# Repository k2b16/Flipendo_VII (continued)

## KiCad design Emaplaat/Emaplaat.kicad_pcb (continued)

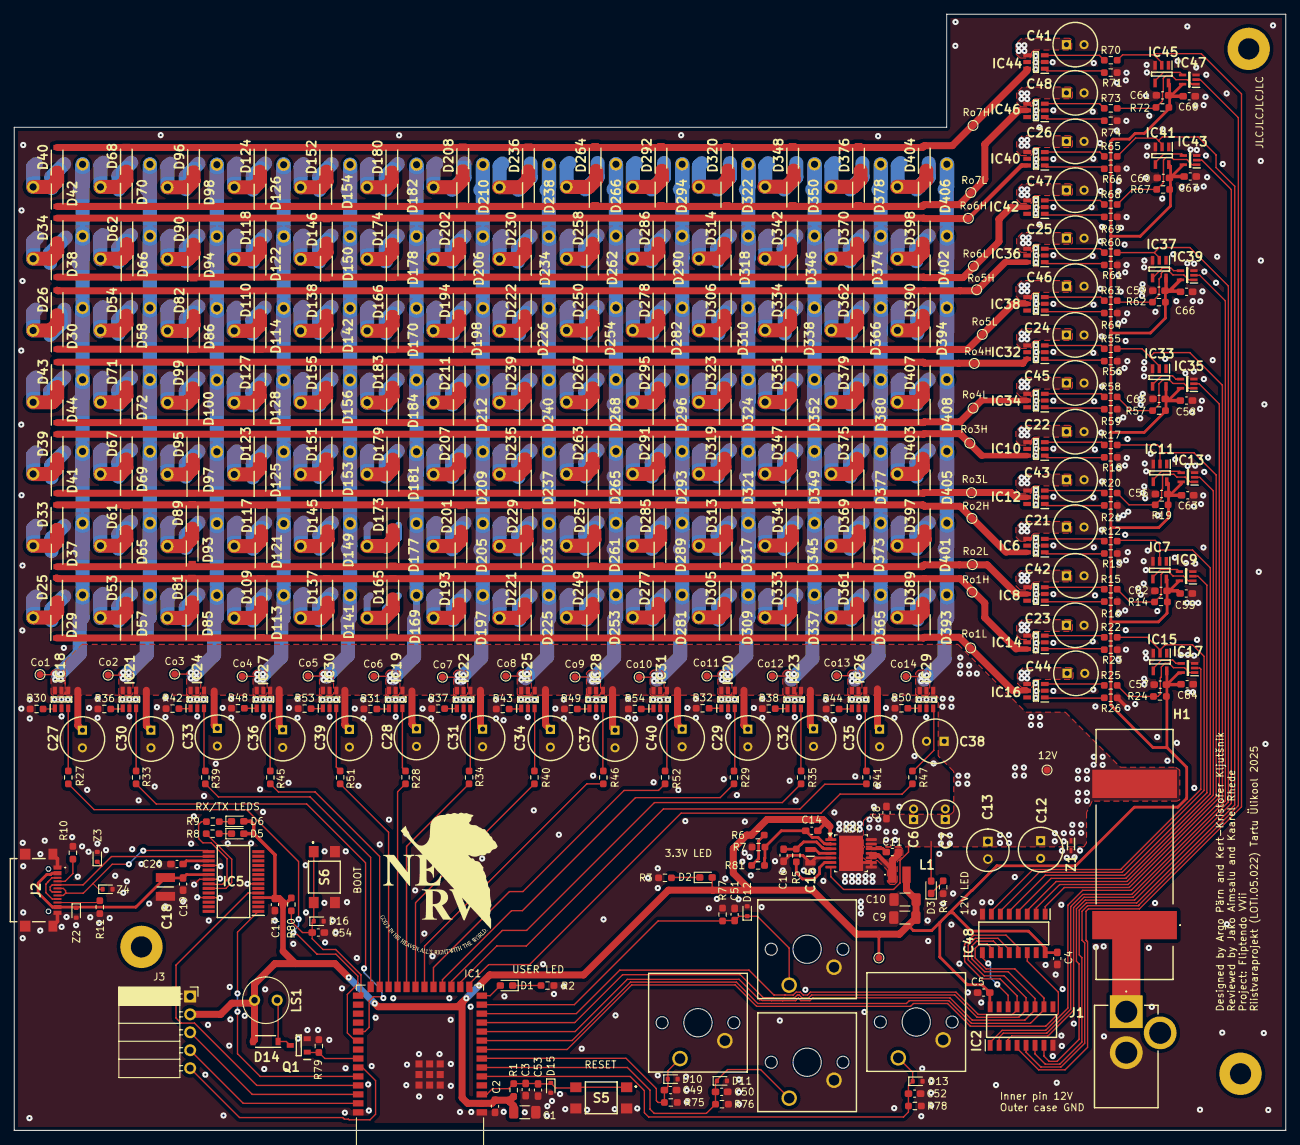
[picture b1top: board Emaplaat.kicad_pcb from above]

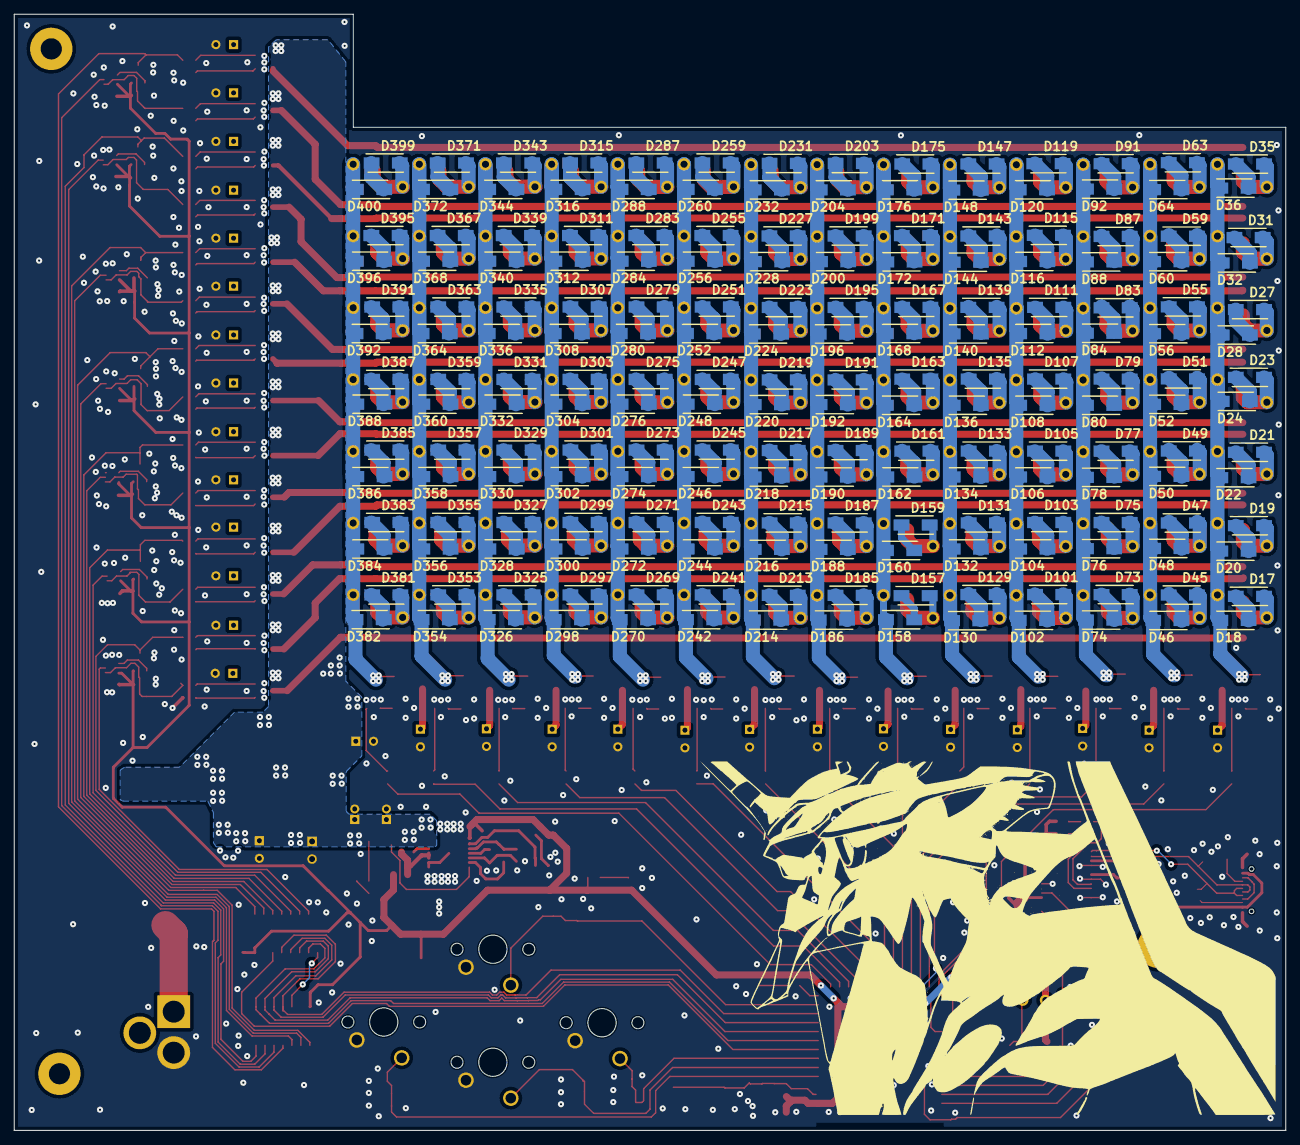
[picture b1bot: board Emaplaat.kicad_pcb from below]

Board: 2 copper layers, 180.0 x 158.0 mm, 664 parts (196 on the bottom side), 367 nets.

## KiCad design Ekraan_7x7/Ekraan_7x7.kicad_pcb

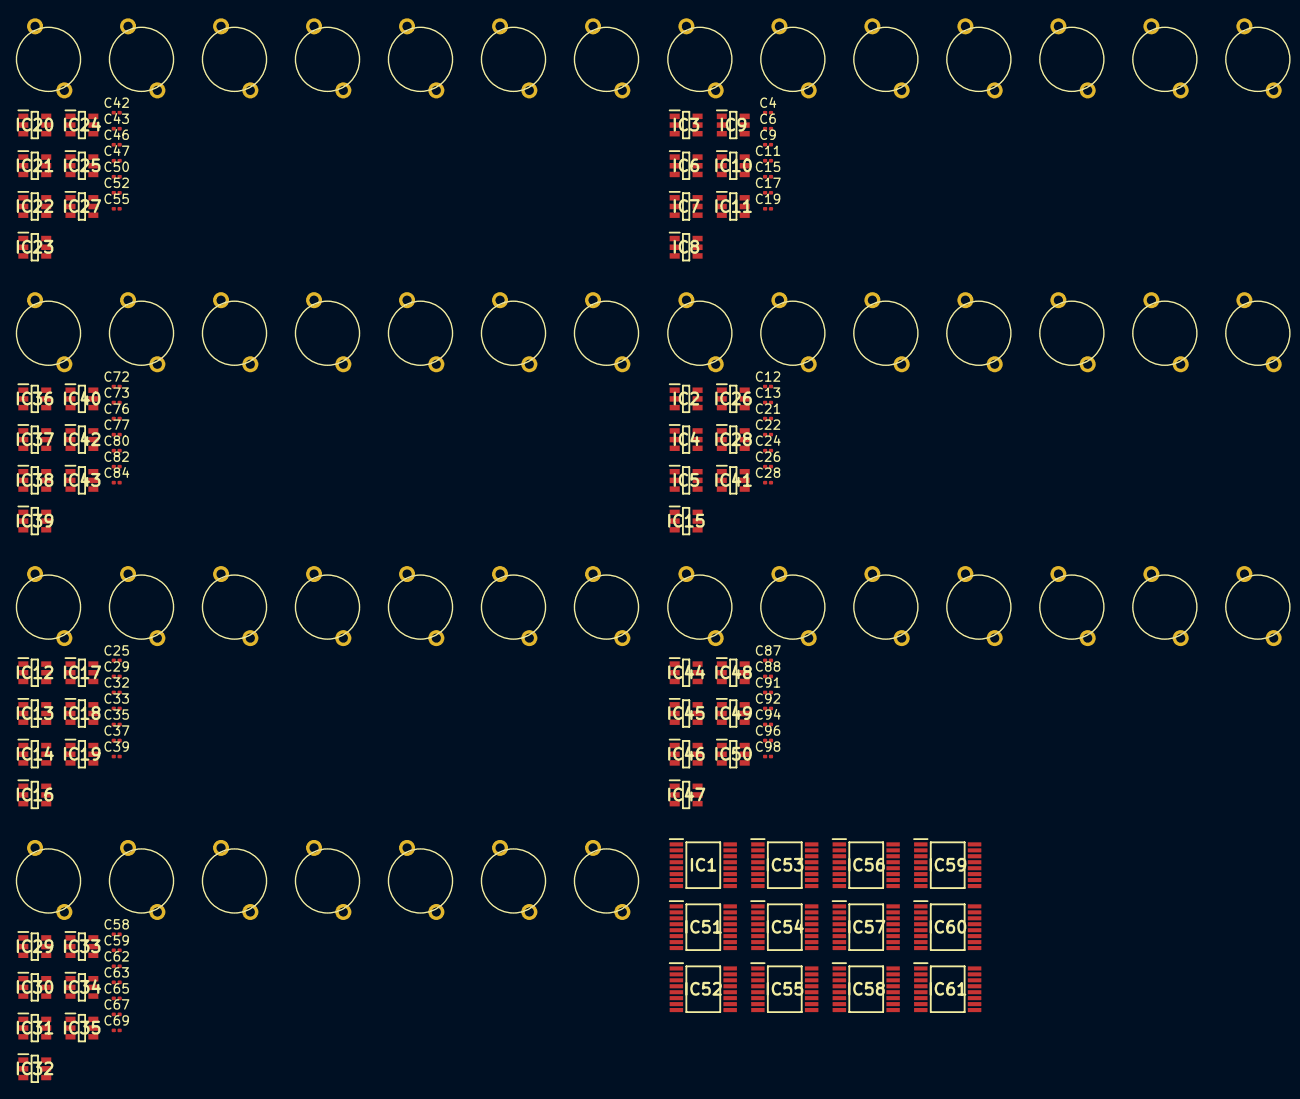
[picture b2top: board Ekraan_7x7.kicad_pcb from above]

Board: 2 copper layers, 117 parts (0 on the bottom side), 117 nets, no tracks yet.

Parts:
C4, C6, C9, C11, C12, C13, C15, C17, C19, C21, C22, C24, C25, C26, C28, C29, C32, C33, C35, C37, C39, C42, C43, C46, C47, C50, C52, C55, C58, C59, C62, C63, C65, C67, C69, C72, C73, C76, C77, C80, C82, C84, C87, C88, C91, C92, C94, C96, C98: 20u; C_0201_0603Metric
IC1, IC51, IC52, IC53, IC54, IC55, IC56, IC57, IC58, IC59, IC60, IC61: 74HC595PW-Q100,118; SOP65P640X110-16N
IC2, IC3, IC4, IC5, IC6, IC7, IC8, IC9, IC10, IC11, IC12, IC13, IC14, IC15, IC16, IC17, IC18, IC19, IC20, IC21, IC22, IC23, IC24, IC25, IC26, IC27, IC28, IC29, IC30, IC31, IC32, IC33, IC34, IC35, IC36, IC37, IC38, IC39, IC40, IC41, IC42, IC43, IC44, IC45, IC46, IC47, IC48, IC49, IC50: 1EDN7550BXTSA1; SOT95P280X145-6N
U1, U2, U3, U4, U5, U6, U7: 1EDN7550BXTSA1; 7_flip_dots

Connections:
3V3: IC1.16 (VCC), IC51.16 (VCC), IC52.16 (VCC), IC53.16 (VCC), IC54.16 (VCC), IC55.16 (VCC), IC56.16 (VCC), IC57.16 (VCC), IC58.16 (VCC), IC59.16 (VCC), IC60.16 (VCC), IC61.16 (VCC)
12V: IC2.4 (VDD), IC3.4 (VDD), IC4.4 (VDD), IC5.4 (VDD), IC6.4 (VDD), IC7.4 (VDD), IC8.4 (VDD), IC9.4 (VDD), IC10.4 (VDD), IC11.4 (VDD), IC12.4 (VDD), IC13.4 (VDD), IC14.4 (VDD), IC15.4 (VDD), IC16.4 (VDD), IC17.4 (VDD), IC18.4 (VDD), IC19.4 (VDD), IC20.4 (VDD), IC21.4 (VDD), IC22.4 (VDD), IC23.4 (VDD), IC24.4 (VDD), IC25.4 (VDD), IC26.4 (VDD), IC27.4 (VDD), IC28.4 (VDD), IC29.4 (VDD), IC30.4 (VDD), IC31.4 (VDD), IC32.4 (VDD), IC33.4 (VDD), IC34.4 (VDD), IC35.4 (VDD), IC36.4 (VDD), IC37.4 (VDD), IC38.4 (VDD), IC39.4 (VDD), IC40.4 (VDD), IC41.4 (VDD), IC42.4 (VDD), IC43.4 (VDD), IC44.4 (VDD), IC45.4 (VDD), IC46.4 (VDD), IC47.4 (VDD), IC48.4 (VDD), IC49.4 (VDD), IC50.4 (VDD)
/!MR: IC1.10 (~MR), IC51.10 (~MR), IC52.10 (~MR), IC53.10 (~MR), IC54.10 (~MR), IC55.10 (~MR), IC56.10 (~MR), IC57.10 (~MR), IC58.10 (~MR), IC59.10 (~MR), IC60.10 (~MR), IC61.10 (~MR)
/!OE: IC1.13 (~OE), IC51.13 (~OE), IC52.13 (~OE), IC53.13 (~OE), IC54.13 (~OE), IC55.13 (~OE), IC56.13 (~OE), IC57.13 (~OE), IC58.13 (~OE), IC59.13 (~OE), IC60.13 (~OE), IC61.13 (~OE)
/SHCP: IC1.11 (SHCP), IC51.11 (SHCP), IC52.11 (SHCP), IC53.11 (SHCP), IC54.11 (SHCP), IC55.11 (SHCP), IC56.11 (SHCP), IC57.11 (SHCP), IC58.11 (SHCP), IC59.11 (SHCP), IC60.11 (SHCP), IC61.11 (SHCP)
/STCP: IC1.12 (STCP), IC51.12 (STCP), IC52.12 (STCP), IC53.12 (STCP), IC54.12 (STCP), IC55.12 (STCP), IC56.12 (STCP), IC57.12 (STCP), IC58.12 (STCP), IC59.12 (STCP), IC60.12 (STCP), IC61.12 (STCP)
/array1/FLIXEL_A: C4.2, U1.1 (A1)
/array1/FLIXEL_B: C9.2, U1.2 (B1)
/array1/FLIXEL_C: C15.2, U1.3 (C1)
/array1/FLIXEL_D: C17.2, U1.4 (D1)
/array1/FLIXEL_E: C19.2, U1.5 (E1)
/array1/FLIXEL_F: C6.2, U1.6 (F1)
/array1/FLIXEL_G: C11.2, U1.7 (G1)
/array2/FLIXEL_A: C25.2, U3.1 (A1)
/array2/FLIXEL_B: C32.2, U3.2 (B1)
/array2/FLIXEL_C: C35.2, U3.3 (C1)
/array2/FLIXEL_D: C37.2, U3.4 (D1)
/array2/FLIXEL_E: C39.2, U3.5 (E1)
/array2/FLIXEL_F: C29.2, U3.6 (F1)
/array2/FLIXEL_G: C33.2, U3.7 (G1)
/array3/FLIXEL_A: C42.2, U4.1 (A1)
/array3/FLIXEL_B: C46.2, U4.2 (B1)
/array3/FLIXEL_C: C50.2, U4.3 (C1)
/array3/FLIXEL_D: C52.2, U4.4 (D1)
/array3/FLIXEL_E: C55.2, U4.5 (E1)
/array3/FLIXEL_F: C43.2, U4.6 (F1)
/array3/FLIXEL_G: C47.2, U4.7 (G1)
/array4/FLIXEL_A: C58.2, U5.1 (A1)
/array4/FLIXEL_B: C62.2, U5.2 (B1)
/array4/FLIXEL_C: C65.2, U5.3 (C1)
/array4/FLIXEL_D: C67.2, U5.4 (D1)
/array4/FLIXEL_E: C69.2, U5.5 (E1)
/array4/FLIXEL_F: C59.2, U5.6 (F1)
/array4/FLIXEL_G: C63.2, U5.7 (G1)
/array5/FLIXEL_A: C72.2, U6.1 (A1)
/array5/FLIXEL_B: C76.2, U6.2 (B1)
/array5/FLIXEL_C: C80.2, U6.3 (C1)
/array5/FLIXEL_D: C82.2, U6.4 (D1)
/array5/FLIXEL_E: C84.2, U6.5 (E1)
/array5/FLIXEL_F: C73.2, U6.6 (F1)
/array5/FLIXEL_G: C77.2, U6.7 (G1)
/array6/FLIXEL_A: C87.2, U7.1 (A1)
/array6/FLIXEL_B: C91.2, U7.2 (B1)
/array6/FLIXEL_C: C94.2, U7.3 (C1)
/array6/FLIXEL_D: C96.2, U7.4 (D1)
/array6/FLIXEL_E: C98.2, U7.5 (E1)
/array6/FLIXEL_F: C88.2, U7.6 (F1)
/array6/FLIXEL_G: C92.2, U7.7 (G1)
/array/FLIXEL_A: C12.2, U2.1 (A1)
/array/FLIXEL_B: C21.2, U2.2 (B1)
/array/FLIXEL_C: C24.2, U2.3 (C1)
/array/FLIXEL_D: C26.2, U2.4 (D1)
/array/FLIXEL_E: C28.2, U2.5 (E1)
/array/FLIXEL_F: C13.2, U2.6 (F1)
/array/FLIXEL_G: C22.2, U2.7 (G1)
AGND: IC1.8 (GND), IC51.8 (GND), IC52.8 (GND), IC53.8 (GND), IC54.8 (GND), IC55.8 (GND), IC56.8 (GND), IC57.8 (GND), IC58.8 (GND), IC59.8 (GND), IC60.8 (GND), IC61.8 (GND)
unnamed: IC1.9 (Q7S), IC51.14 (DS)
unnamed: C12.1, IC2.5 (OUT_SRC), IC2.6 (OUT_SNK)
unnamed: C4.1, IC3.5 (OUT_SRC), IC3.6 (OUT_SNK)
unnamed: C13.1, IC4.5 (OUT_SRC), IC4.6 (OUT_SNK)
unnamed: C21.1, IC5.5 (OUT_SRC), IC5.6 (OUT_SNK)
unnamed: C6.1, IC6.5 (OUT_SRC), IC6.6 (OUT_SNK)
unnamed: C9.1, IC7.5 (OUT_SRC), IC7.6 (OUT_SNK)
unnamed: C11.1, IC8.5 (OUT_SRC), IC8.6 (OUT_SNK)
unnamed: C15.1, IC9.5 (OUT_SRC), IC9.6 (OUT_SNK)
unnamed: C17.1, IC10.5 (OUT_SRC), IC10.6 (OUT_SNK)
unnamed: C19.1, IC11.5 (OUT_SRC), IC11.6 (OUT_SNK)
unnamed: C25.1, IC12.5 (OUT_SRC), IC12.6 (OUT_SNK)
unnamed: C29.1, IC13.5 (OUT_SRC), IC13.6 (OUT_SNK)
unnamed: C32.1, IC14.5 (OUT_SRC), IC14.6 (OUT_SNK)
unnamed: C24.1, IC15.5 (OUT_SRC), IC15.6 (OUT_SNK)
unnamed: C33.1, IC16.5 (OUT_SRC), IC16.6 (OUT_SNK)
unnamed: C35.1, IC17.5 (OUT_SRC), IC17.6 (OUT_SNK)
unnamed: C37.1, IC18.5 (OUT_SRC), IC18.6 (OUT_SNK)
unnamed: C39.1, IC19.5 (OUT_SRC), IC19.6 (OUT_SNK)
unnamed: C42.1, IC20.5 (OUT_SRC), IC20.6 (OUT_SNK)
unnamed: C43.1, IC21.5 (OUT_SRC), IC21.6 (OUT_SNK)
unnamed: C46.1, IC22.5 (OUT_SRC), IC22.6 (OUT_SNK)
unnamed: C47.1, IC23.5 (OUT_SRC), IC23.6 (OUT_SNK)
unnamed: C50.1, IC24.5 (OUT_SRC), IC24.6 (OUT_SNK)
unnamed: C52.1, IC25.5 (OUT_SRC), IC25.6 (OUT_SNK)
unnamed: C22.1, IC26.5 (OUT_SRC), IC26.6 (OUT_SNK)
unnamed: C55.1, IC27.5 (OUT_SRC), IC27.6 (OUT_SNK)
unnamed: C26.1, IC28.5 (OUT_SRC), IC28.6 (OUT_SNK)
unnamed: C58.1, IC29.5 (OUT_SRC), IC29.6 (OUT_SNK)
unnamed: C59.1, IC30.5 (OUT_SRC), IC30.6 (OUT_SNK)
unnamed: C62.1, IC31.5 (OUT_SRC), IC31.6 (OUT_SNK)
unnamed: C63.1, IC32.5 (OUT_SRC), IC32.6 (OUT_SNK)
unnamed: C65.1, IC33.5 (OUT_SRC), IC33.6 (OUT_SNK)
unnamed: C67.1, IC34.5 (OUT_SRC), IC34.6 (OUT_SNK)
unnamed: C69.1, IC35.5 (OUT_SRC), IC35.6 (OUT_SNK)
unnamed: C72.1, IC36.5 (OUT_SRC), IC36.6 (OUT_SNK)
unnamed: C73.1, IC37.5 (OUT_SRC), IC37.6 (OUT_SNK)
unnamed: C76.1, IC38.5 (OUT_SRC), IC38.6 (OUT_SNK)
unnamed: C77.1, IC39.5 (OUT_SRC), IC39.6 (OUT_SNK)
unnamed: C80.1, IC40.5 (OUT_SRC), IC40.6 (OUT_SNK)
unnamed: C28.1, IC41.5 (OUT_SRC), IC41.6 (OUT_SNK)
unnamed: C82.1, IC42.5 (OUT_SRC), IC42.6 (OUT_SNK)
unnamed: C84.1, IC43.5 (OUT_SRC), IC43.6 (OUT_SNK)
unnamed: C87.1, IC44.5 (OUT_SRC), IC44.6 (OUT_SNK)
unnamed: C88.1, IC45.5 (OUT_SRC), IC45.6 (OUT_SNK)
unnamed: C91.1, IC46.5 (OUT_SRC), IC46.6 (OUT_SNK)
unnamed: C92.1, IC47.5 (OUT_SRC), IC47.6 (OUT_SNK)
unnamed: C94.1, IC48.5 (OUT_SRC), IC48.6 (OUT_SNK)
unnamed: C96.1, IC49.5 (OUT_SRC), IC49.6 (OUT_SNK)
unnamed: C98.1, IC50.5 (OUT_SRC), IC50.6 (OUT_SNK)
unnamed: IC51.9 (Q7S), IC52.14 (DS)
unnamed: IC52.9 (Q7S), IC53.14 (DS)
unnamed: IC53.9 (Q7S), IC54.14 (DS)
unnamed: IC54.9 (Q7S), IC55.14 (DS)
unnamed: IC55.9 (Q7S), IC56.14 (DS)
unnamed: IC56.9 (Q7S), IC59.14 (DS)
unnamed: IC57.14 (DS), IC59.9 (Q7S)
unnamed: IC57.9 (Q7S), IC60.14 (DS)
unnamed: IC58.14 (DS), IC60.9 (Q7S)
unnamed: IC58.9 (Q7S), IC61.14 (DS)
PGND: IC2.2 (GND), IC3.2 (GND), IC4.2 (GND), IC5.2 (GND), IC6.2 (GND), IC7.2 (GND), IC8.2 (GND), IC9.2 (GND), IC10.2 (GND), IC11.2 (GND), IC12.2 (GND), IC13.2 (GND), IC14.2 (GND), IC15.2 (GND), IC16.2 (GND), IC17.2 (GND), IC18.2 (GND), IC19.2 (GND), IC20.2 (GND), IC21.2 (GND), IC22.2 (GND), IC23.2 (GND), IC24.2 (GND), IC25.2 (GND), IC26.2 (GND), IC27.2 (GND), IC28.2 (GND), IC29.2 (GND), IC30.2 (GND), IC31.2 (GND), IC32.2 (GND), IC33.2 (GND), IC34.2 (GND), IC35.2 (GND), IC36.2 (GND), IC37.2 (GND), IC38.2 (GND), IC39.2 (GND), IC40.2 (GND), IC41.2 (GND), IC42.2 (GND), IC43.2 (GND), IC44.2 (GND), IC45.2 (GND), IC46.2 (GND), IC47.2 (GND), IC48.2 (GND), IC49.2 (GND), IC50.2 (GND), U1.8 (A2), U1.9 (B2), U1.10 (C2), U1.11 (D2), U1.12 (E2), U1.13 (F2), U1.14 (G2), U2.8 (A2), U2.9 (B2), U2.10 (C2), U2.11 (D2), U2.12 (E2), U2.13 (F2), U2.14 (G2), U3.8 (A2), U3.9 (B2), U3.10 (C2), U3.11 (D2), U3.12 (E2), U3.13 (F2), U3.14 (G2), U4.8 (A2), U4.9 (B2), U4.10 (C2), U4.11 (D2), U4.12 (E2), U4.13 (F2), U4.14 (G2), U5.8 (A2), U5.9 (B2), U5.10 (C2), U5.11 (D2), U5.12 (E2), U5.13 (F2), U5.14 (G2), U6.8 (A2), U6.9 (B2), U6.10 (C2), U6.11 (D2), U6.12 (E2), U6.13 (F2), U6.14 (G2), U7.8 (A2), U7.9 (B2), U7.10 (C2), U7.11 (D2), U7.12 (E2), U7.13 (F2), U7.14 (G2)

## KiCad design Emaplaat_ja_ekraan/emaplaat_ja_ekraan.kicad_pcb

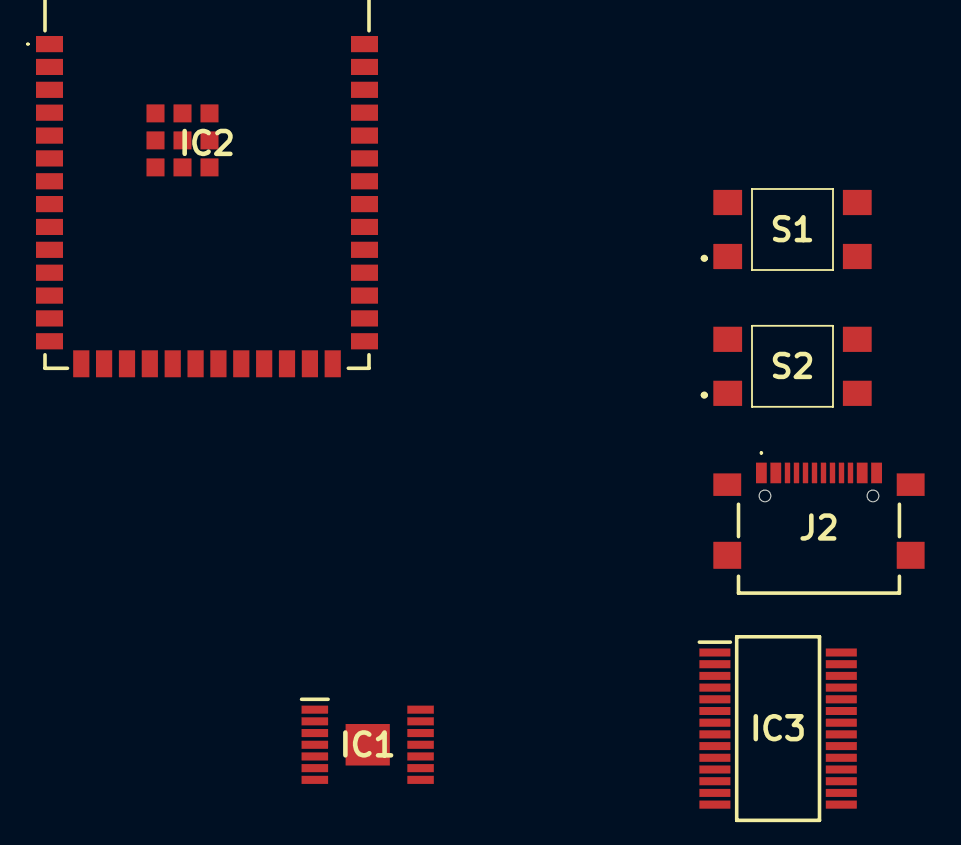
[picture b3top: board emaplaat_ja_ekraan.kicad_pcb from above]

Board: 2 copper layers, 6 parts (0 on the bottom side), 12 nets, no tracks yet.

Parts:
IC1: TPS54429PWPR; SOP65P640X120-15N
IC2: ESP32-S3-WROOM-2-N32R16V; ESP32S3WROOM2N32R16V
IC3: FT232RNL-TUBE; SOP65P780X200-28N
J2: USB4216-03-A; USB421603A
S1, S2: TL3305BF100QG; TL3305BF160QG

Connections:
3V3: IC1.1 (VO), IC2.2 (3V3)
/BOOT: IC2.16 (IO46), S2.1, S2.2
/EN: IC2.3 (EN), S1.1, S1.2
AGND: IC1.5 (GND_1), IC2.1 (GND), IC2.40 (GND), IC2.41 (GND), IC2.42 (GND), IC2.43 (GND), IC2.44 (GND), IC2.45 (GND), IC2.46 (GND), IC2.47 (GND), IC2.48 (GND), IC2.49 (GND), IC3.7 (GND), IC3.18 (GND_2), IC3.21 (GND_3), IC3.25 (AGND), J2.A1 (GND_1), J2.A5 (CC1), J2.A8 (SBU1), J2.B1 (GND_2), J2.B5 (CC2), J2.B8 (SBU2), J2.G1 (GND_3), J2.G2 (GND_4), J2.G3 (GND_5), J2.G4 (GND_6), S1.3, S1.4, S2.3, S2.4
unnamed: IC1.7 (EN), IC1.13 (VIN1), IC1.14 (VIN2)
unnamed: IC1.10 (SW1), IC1.11 (SW2)
unnamed: IC2.28 (NC_1), IC2.29 (NC_2), IC2.30 (NC_3)
unnamed: IC3.8 (NC_1), IC3.24 (NC_2)
unnamed: IC3.16 (USBDM), J2.A7 (DN1), J2.B7 (DN2)
unnamed: IC3.15 (USBDP), J2.A6 (DP1), J2.B6 (DP2)
unnamed: IC3.4 (VCCIO), IC3.20 (VCC), J2.A4 (VBUS_1), J2.B4 (VBUS_2)
PGND: IC1.8 (PGND1), IC1.9 (PGND2), IC1.15 (PAD)

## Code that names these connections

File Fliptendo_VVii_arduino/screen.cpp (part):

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  LOW,
};

const uint8_t ROW1_L = 8;
const uint8_t ROW1_H = 9;
const uint8_t ROW2_L = 10;
const uint8_t ROW2_H = 11;
const uint8_t ROW3_L = 12;
const uint8_t ROW3_H = 13;
const uint8_t ROW4_L = 14;
const uint8_t ROW4_H = 6;
const uint8_t ROW5_L = 5;
const uint8_t ROW5_H = 4;
const uint8_t ROW6_L = 0;
const uint8_t ROW6_H = 1;
const uint8_t ROW7_L = 2;
const uint8_t ROW7_H = 3;

const uint8_t ROWS_H[] = {
  0, // unused
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
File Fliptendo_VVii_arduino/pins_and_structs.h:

#ifndef PINS_AND_STRUCTS_H
#define PINS_AND_STRUCTS_H

#include "cstdint"

/* joystick */
typedef struct {
  uint16_t rx;
  uint16_t ry;
  uint8_t sw;
} joystick_st;

/* buttons */
typedef struct {
  int up;
  int down;
  int left;
  int right;
} buttons_st;

/* pins */
const int UP = 4; // UP = 19 (old pin)
const int DOWN = 6;
const int LEFT = 7;
const int RIGHT = 5;

const int JS_SW = 42;
const int JS_RY = 1;
const int JS_RX = 2;

const int USER_LED = 20;

const int COL_1 = 39;
const int COL_2 = 38;
const int COL_3 = 45;
const int COL_4 = 48;
const int COL_5 = 47;
const int COL_6 = 21;
const int COL_7 = 14;
const int COL_8 = 13;
const int COL_9 = 12;
const int COL_10 = 11;
const int COL_11 = 10;
const int COL_12 = 9;
const int COL_13 = 46;
const int COL_14 = 3;

const int not_OE = 8;
const int STCP = 18;
const int SHCP = 17;
const int not_MR = 16;
const int DS = 15;

const int BUZZER = 41;

#endif

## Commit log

2025-10-09 type shi
2025-10-12 try again
2025-10-13 yabbadabbadooo
2025-10-13 yabbbababababab
2025-10-13 awsedrtfg
2025-10-13 aaaaaaaaaaaaaaaga
2025-10-14 altium on päris keeruline
2025-10-14 ASDFG
2025-10-14 sdfggggggggggggggggggggggg
2025-10-14 Kicad project
2025-10-14 librad ja asjalibrad ja asjadd
2025-10-14 qwertytrerthgtrew
2025-10-14 qwertyuiiiiuytrewwwertyuiuytrewertyuytrew
2025-10-14 clean up T-T
2025-10-14 dev esimen =w=
2025-10-14 Toomas Plank
2025-10-14 Urmas Tamm
2025-10-15 cleanoupp T__W
2025-10-15 qqwertrewasdfgfdsdfgfdsdfgfdsasdfghgfdsdfghgfdsasdfghgfdsasdfgfew3
2025-10-15 Getamine addiction
2025-10-15 Koomas Plank
2025-10-15 enamvahem valmis
2025-10-15 kerge cleanup
2025-10-15 SEE SITT
2025-10-15 Abels
2025-11-06 qwerghhgfdsdfghqwerghhgfdsdfghjj
2025-11-06 fliptendo gameboy type shi
2025-11-11 ketamine addict
2025-11-12 T________T Heiki Tammemägi
2025-11-17 skeem v2 kinda valmis, simulatsioon ka tehtud
2025-11-17 simulatsiooni check 50u kondekaid vaja
2025-11-18 fsfsfe
2025-11-18 Kaareli tagasiside
2025-11-20 git stuff
2025-11-20 cleanup
2025-11-20 fixup
2025-11-20 uuem versioon
2025-11-20 T__T
2025-11-21 eemaldasin mõttetud skeemid
2025-11-21 Kaareli tagasiside ka
2025-11-21 3V3 voolud kontrollitud
2025-11-23 added comments to capacitors of UART bridge
2025-11-23 ts fire commit
2025-11-23 okei fix
2025-11-24 Kaareli kolmas tagasiside
2025-11-25 jajald
2025-11-25 skeem korras
2025-11-25 trükkplaat algus
2025-11-25 trükkplaat valmis võib Abelisle helistada
2025-11-26 3 flixli arrayd tehtud
2025-11-26 6 flixel arrayd tehtud
2025-11-26 ekraan maatriks rajad veetud
2025-11-26 veergude toide veetud
2025-11-26 ekraani ridade võim veetud
2025-11-26 algeline paigutus
2025-11-26 veel algelisem paigutus
2025-11-27 väike footprint parandus
2025-11-27 foot print parandus
2025-11-28 bonkers
2025-11-30 :TTT: WWKWKWWKWWKWWKWKWWKWW !"]¤3!E_#1%FV{'14¤#(%2
2025-11-30 trükkplaat v0 valmis
2025-12-01 trükkplaat v0.1 parandused + 3d failid vaja leid
2025-12-01 jalajäljed
2025-12-01 lelelelel
2025-12-01 trükkplaat v0.2 3d failid enamus olemas
2025-12-01 added MX footprint and 3d file
2025-12-01 added MX footprint and 3d symbol
2025-12-02 ühe takisti muudatus
2025-12-02 v1.0 aga muudatusi on vaja veel teha
2025-12-03 natuke parandusi
2025-12-05 Added electrolytic capacitors and 12V rated ESD diode
2025-12-07 Lisasin kondensaatorid, mis on >3.3u footprindi ja sümbolid. Sammuti liigutasin ESP32 ja USC-C ühendused plaadi äärtele
2025-12-07 v1.1 kuid veel pooleli
2025-12-07 v1.2 peaaegu valmis, aint 5V esd dioodid vaja lisada
2025-12-08 v1.2 bootstrapping pin parandus
2025-12-09 v1.3 pooleli
2025-12-09 v1.4 peaagu
2025-12-09 v1.5 valmis, juhendajad andsid rohelise tule
2025-12-09 v2.1 parandused
2025-12-09 v2.2 valmis
2025-12-09 v2.3 VALMIS
2025-12-13 uus BOM ja asendasin 0.1uF kondeka
2025-12-14 v2.4 nihkeregistri vahetus
2025-12-15 added missing 3d models
2025-12-15 pro parandus
2025-12-18 v3.0 Abeltoni tagaside implement
2025-12-18 v3.3 Abeltoni tagasiside veelkord
2026-01-11 arduino kood
2026-01-11 YBG, young black and gifted
2026-01-11 column1 test
2026-01-18 ino koodile shift reg asjad
2026-01-20 ard-ui-no getamineˇˇ
2026-01-22 ard kood
2026-01-27 ultra mega tony soprano
2026-01-27 ekraani kerge animatsioon
2026-01-27 lil code cleanup
2026-01-28 keraanigge kood
2026-01-29 arrow timing game done
2026-01-29 game + picutres
2026-01-30 homemade flixel array models
